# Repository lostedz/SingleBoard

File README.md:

# 68000 Verilog CPU

Target: **Xilinx Spartan-6 XC6SLX16 / FTG256 at 50 MHz** (speed grade -2
provisional). See `fpga/spartan6/README.md` for the ISE/XST
synthesis flow and board integration requirements.

An **MT48LC16M16A2-75 SDRAM controller** is included for the same 50 MHz clock.
See [SDRAM integration](docs/sdram.md) for its 32 MiB address mapping, CPU bus
connection, Spartan-6 clock forwarding, initialization and refresh behavior.
Run its standalone and CPU integration tests with `python scripts/test_sdram.py`.

A [memory-mapped UART](docs/uart.md) is available at **0xFF0000**, defaulting
to **115200 baud, 8N1** at 50 MHz. It includes TX/RX buffering, receive error
flags and optional interrupts. Run `python scripts/test_uart.py` for serial
and 68000 interrupt/echo tests.

A [schematic and board](hardware/README.md) for this target are in `hardware/`, as
a KiCad 10 project covering power, FPGA supply and configuration, the boot flash,
the SDRAM and the UART/clock/reset front panel. Both are generated:
`python scripts/gen_schematic.py` emits the drawing and the matching
`fpga/spartan6/singleboard.ucf` from one ball-assignment table, and
`python scripts/gen_pcb.py` builds the board from the schematic's own netlist —
a 120 × 90 mm four-layer placement whose floorplan follows which bank each
block's balls are in. The schematic passes ERC, the board passes DRC, and the
copper has been read back and compared to the assignment table. It is still a
concept: **the board has no tracks on it**, and there has been no ISE run and no
hardware validation.

`rtl/m68000.v` provides a synthesizable Verilog-2005 CPU for FPGA integration,
based on Frederic Requin's ISC-licensed [J68](https://github.com/fredrequin/j68_cpu).
The execution engine is vendored J68 RTL, not a newly written CPU. Local work
adds a 24-bit address interface, portable inferred memories, and executable
self-checking integration tests.

J68 implements the 68000 instruction set using a microcoded 16-bit datapath:
eight 32-bit data registers, eight address registers, separate user and
supervisor stacks, condition codes, effective-address decoding, multiply/divide,
traps, and autovectored interrupts. See `rtl/j68/PROVENANCE.md` for the pinned
revision and changes.

## Interface

All signals use one rising-edge clock. Inputs must be synchronous to `clk`.

| Signal | Meaning |
| --- | --- |
| `clk`, `reset` | Clock and active-high reset; hold reset for at least two clock edges and deassert synchronously |
| `clk_en` | CPU step enable; tie high for continuous execution |
| `ipl_n[2:0]` | Active-low encoded interrupt level; `111` is no interrupt, `101` is level 2 |
| `bus_valid` | Pending memory transaction |
| `bus_write` | 1 for write, 0 for read; meaningful while valid |
| `bus_addr[23:0]` | Byte address, including the low bit; high internal address bits are truncated to the 68000's 24-bit address space |
| `bus_be[1:0]` | Active-high byte lanes: bit 1 selects the even-address/high byte, bit 0 the odd-address/low byte |
| `bus_wdata[15:0]` | Write data already positioned in the selected lanes |
| `bus_rdata[15:0]` | Read data for the aligned word containing `bus_addr` |
| `bus_ready` | Memory acknowledgement; reads must have valid data on the completion edge |
| `bus_fc[2:0]` | J68 function-code output (user/supervisor, data/program/vector) |
| `debug_pc`, `debug_sr` | Internal 32-bit program counter and 16-bit status register |

A transfer completes on a rising edge when **`clk_en && bus_valid && bus_ready`**.
The memory slave must use that same condition for write side effects. Address,
direction, lanes, function code and write data remain stable during a pending
transaction, including CPU pauses. A slave may keep `bus_ready` high, or delay
it for any number of cycles. If the CPU is paused, retain read data/acknowledgement
until an enabled completion edge. Reset cancels a pending transaction.

Memory is big-endian. A longword uses two word transactions, high word first
for normal forward accesses. Fetch the initial SSP from addresses 0–3 and
initial PC from 4–7. Supply a valid reset-vector table and executable memory.
The testbench is a complete example memory slave.

## Build and test

Run from the project root so `$readmemb` can locate `rtl/j68/*.mem`. Include
every source in `rtl/files.f` and select `m68000` as the synthesis top. Memory
initialization must be supported by the target FPGA/toolchain; this is not
an ASIC ROM implementation. There are no vendor primitives or SystemVerilog
dependencies in the RTL.

With Python 3 and Icarus Verilog (`iverilog` and `vvp`) on PATH:

```sh
python scripts/test.py
python scripts/test.py --vcd
```

The runner also recognizes a local portable Windows installation in
`.tools/bin`. Test firmware is committed as `tests/smoke.hex`; an assembler
is not needed to run tests. To rebuild it with vasm:

```sh
vasmm68k -m68000 -Fbin -o build/smoke.bin tests/smoke.asm
python scripts/rom_to_hex.py
```

The self-checking program covers reset vectors, MOVE and MOVEQ, big-endian
byte/word/long transfers, postincrement/predecrement/indexed addressing,
arithmetic and overflow/carry/zero/negative flags, logic, shifts, bit operations,
DBRA, subroutine calls, signed/unsigned multiply/divide, MOVEM, TRAP/RTE,
STOP wakeup, and level-2 interrupts. It runs twice per simulation to check
reset recovery, with zero/one/seven wait cycles, periodic CPU pauses, and
deterministic irregular pauses with thirteen wait cycles. The bench also
checks request stability while stalled. Any failure or missing PASS fails
the Python runner, including with older VVP versions that return zero on `$fatal`.

## Compatibility limits

- This is not cycle-exact or a pin-compatible replacement for a physical MC68000.
  The interface is synchronous valid/ready, without AS/UDS/LDS, bus arbitration,
  a peripheral E clock, or a locked bus-cycle signal. External logic is needed
  for such system interfaces; multiprocessor atomic TAS is not provided.
- Bus-error exceptions and externally supplied interrupt vectors are not
  implemented. Interrupts use internal autovectors, without an external IACK cycle.
- J68's `RESET` opcode enters its CPU initialization routine; it does not emit
  the original processor's external peripheral-reset pulse.
- Address-error and other exception machinery comes from upstream. The included
  tests are smoke/integration coverage, not exhaustive instruction or exception
  conformance certification. No FPGA synthesis, timing closure, or hardware
  validation has been performed for this project.

Licensed under ISC; upstream attribution and licensing are retained.

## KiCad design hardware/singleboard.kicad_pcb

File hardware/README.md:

# SingleBoard 68K schematic and board

A KiCad schematic and board for the target the rest of this repository aims at: the
J68-derived 68000 soft CPU running inside an **XC6SLX16-FTG256** at 50 MHz, with the
**MT48LC16M16A2-75** SDRAM of [docs/sdram.md](../docs/sdram.md) and the 3.3 V
logic-level UART of [docs/uart.md](../docs/uart.md).

**This is a concept.** The schematic has not been simulated, fabricated or reviewed
by anyone, and the board is **placed but not routed** — it has no tracks on it at
all. Nothing here has been checked against silicon. Read
[Before you build one](#before-you-build-one) before spending money on it.

## Opening it

Open `singleboard.kicad_pro` in KiCad 10 (the files are written in KiCad 10's
formats: schematic `version 20260101`, board `version 20260206`).
`singleboard.pdf` is the drawing plotted out and `singleboard-pcb.pdf` is the
board's layer plot, if you only want to read them.

Project-specific symbols live in `symbols/singleboard.kicad_sym` and are found
through `sym-lib-table`. Everything else, footprints included, comes from KiCad's
stock libraries, so the board carries no local footprint library.

## Regenerating

Neither file is drawn by hand. The schematic comes first, and the board is
generated from the schematic's own netlist:

```sh
python scripts/gen_schematic.py
python scripts/gen_pcb.py
```

The first run writes the six sheets, the project symbol library, the project file
**and** `fpga/spartan6/singleboard.ucf`. The ball assignment exists once — the
SDRAM half is read from [sp6_SDRAM.ucf](../fpga/spartan6/sp6_SDRAM.ucf), the rest is
in the `BANK0_MAP` / `BANK2_MAP` tables at the top of the script — so the drawing and
the ISE constraints cannot drift apart. Edit the source, re-run; do not edit the
`.kicad_sch`, `.kicad_pcb`, `.kicad_pro` or `singleboard.ucf` by hand.

The second run exports the netlist from the schematic with `kicad-cli` and builds
the board from it, so footprints, references and nets cannot drift away from the
drawing either. It needs KiCad 10 installed and re-executes itself under KiCad's
bundled Python to get `pcbnew`; set `KICAD_HOME` if it is not in the usual place.

Before it draws anything the generator checks that every assigned ball exists on
the FTG256, is an I/O rather than a supply ball, and that the SDRAM sits wholly in
one bank. It fails loudly rather than emitting a wrong drawing.

The FPGA symbol itself is built from `sources/XC6SLX16-FTG256.lib`, so its 256
ball names and numbers are not retyped anywhere.

UUIDs are derived deterministically from sheet and reference names in both
generators, so regenerating an unchanged design produces byte-identical files.
`pcbnew` hands out random ones and sorts footprints by them, so the board
generator reseeds every item from its reference designator before saving.

## Sheets

| Page | Sheet | Contents |
| --- | --- | --- |
| 1 | `singleboard` | Overview and sheet index |
| 2 | `power` | 5 V input protection, 3.3 V and 1.2 V buck converters, test points |
| 3 | `fpga_core` | FPGA supply and ground balls, decoupling, configuration pins, boot flash, JTAG |
| 4 | `fpga_io` | The two I/O bank units, VCCO decoupling (A2 sheet) |
| 5 | `sdram` | MT48LC16M16A2P-75 and its decoupling |
| 6 | `io` | Oscillator, UART header, reset button, status LEDs |

Cross-sheet connectivity is by **global label**; the sheets carry no hierarchy
pins. Every device pin is drawn as a short stub terminated in a label or a power
port, which is the usual style for a part with this many pins and keeps the
generator honest.

## Power

Two rails from a 5 V barrel jack:

| Rail | Source | Feeds |
| --- | --- | --- |
| +3V3 | TPS562200 buck, 100k/30.1k feedback | VCCO banks 0–3, VCCAUX, SDRAM, boot flash, oscillator, LEDs |
| +1V2 | TPS562200 buck, 56.2k/100k feedback | VCCINT |

The input has a 1.1 A polyfuse, a series SS34 for reverse polarity (about 0.4 V
of drop; both bucks accept 4.5 V minimum) and an SMAJ5.0A clamp.

**VCCAUX is run at 3.3 V rather than 2.5 V**, which is what removes the third
rail. The bitstream has to agree, so the generated UCF carries
`CONFIG VCCAUX = 3.3;`.

R3/C3 hold the 3.3 V enable about 100 ms behind the 1.2 V enable, so VCCINT comes
up before VCCO and VCCAUX. This follows the recommended order; confirm against
DS162 whether your device actually requires a sequence.

Decoupling is one 100 nF per supply ball — 8 on VCCINT, 8 on VCCAUX, 20 across the
four VCCO banks, 7 on the SDRAM — plus bulk on each rail. They are only meaningful
if layout puts each one against its ball, which is what the board's
[bypass placement](#bypass-placement) is for.

## Pin assignment

**The SDRAM balls are not chosen here.** All 39 of them are read out of
[sp6_SDRAM.ucf](../fpga/spartan6/sp6_SDRAM.ucf), the constraints file for the
reference Spartan-6 SDRAM board, at generation time. Only the signal names are
translated (`Data[0]` → `SDRAM_DQ0`, `SDCS0` → `SDRAM_CS_N`, and so on); every
`LOC` is taken verbatim, so the schematic follows the physical board rather than
the other way round. Change that file and re-run the generator.

They all land in **bank 3**, and the generator refuses to run if they do not.
Note that the assignment does not line up with the hard memory controller's own
ball names — `SDRAM_DQ0` sits on `IO_L83N_VREF_3`, for instance. That is fine
here: the MCB is not instantiated, and the soft controller in
`rtl/sdram_mt48lc16m16a2.v` drives these as ordinary LVCMOS33 I/O.

Bank 0 carries the 50 MHz clock (on GCLK-capable ball E7), the UART, the reset
button, the four LEDs and the HSWAPEN strap. Bank 2 carries the master-SPI
configuration interface. **Bank 1 is entirely spare**, as is most of bank 0.

`sp6_SDRAM.ucf` also fixes four non-SDRAM pins for its own board — `CLK_50M_IN`
A10, `sys_rst_n` R7, `led_1` T9, `led_2` R9 — which this schematic does *not*
follow; its clock, reset and LEDs are on the bank-0 balls above. If the intent is
to match that board rather than to design a new one, those four should move too.

Unused bank pins carry a no-connect flag. To bring one out later, delete its flag
on the `fpga_io` sheet and add a `LOC` to the UCF.

`R30` (22 Ω) damps the forwarded SDRAM clock. The FPGA-side net is
`SDRAM_CLK_FPGA` and the device-side net is `SDRAM_CLK`;
`rtl/sdram_spartan6_clock.v` drives the FPGA side from an ODDR2 with the clock
inverted so the device samples mid-cycle.

## Configuration

Master SPI from a W25Q32JVSS (32 Mbit; an XC6SLX16 bitstream is about 3.73 Mbit),
with JTAG on a 6-pin 0.1" header in the Digilent order (1 TMS, 2 TDI, 3 TDO,
4 TCK, 5 GND, 6 VREF).

The mode pins are strapped **M[1:0] = 01**. Each strap has a fitted resistor and a
DNP alternate (R16 and R17) so the mode can be changed by rework.
DONE gets the 330 Ω pull-up UG380 asks for; D4 lights while the device is
*un*configured.

## Board

`singleboard.kicad_pcb` is **120 × 90 mm, four layers, placed and planed but with
no tracks on it**. All 129 footprints are down, every pad carries the net the
schematic gives it (bar the barrel jack's unused switched contact), the
planes are poured, and all 220 nets are still ratsnest lines. Routing it is the
next piece of work, not something this file has had.

| Layer | Use |
| --- | --- |
| F.Cu | Components and signal routing |
| In1.Cu (`GND`) | Solid ground plane, 10466 mm² poured |
| In2.Cu (`PWR`) | +3V3 plane with a 1180 mm² +1V2 island cut into it |
| B.Cu | Bypass capacitors, ground pour, signal routing |

Design rules live in `singleboard.kicad_pro` and are sized for an escape out of a
1.0 mm pitch BGA: 0.15 mm track on 0.13 mm clearance with 0.45/0.25 mm vias by
default, and a `Power` class at 0.6 mm track and 0.8/0.4 mm vias for GND, +5V,
+3V3, +1V2 and the two buck switch nodes.

### Floorplan

Nothing about the arrangement is arbitrary — each block sits on the side of the
package its balls are on, which the generator reads out of the same ball map the
schematic uses:

| Block | Where | Why |
| --- | --- | --- |
| SDRAM, `R30` | Left of the FPGA | All 39 SDRAM balls are in bank 3, the −X side |
| Oscillator, reset, LEDs, UART header | Above it | Bank 0 is the −Y side |
| Boot flash, mode straps, JTAG header, PROG | Below it | Bank 2 is the +Y side |
| Both bucks, barrel jack, fuse, TVS, test points | Right-hand column | Bank 1 is entirely spare, so nothing competes for it |

The 1.2 V island on In2.Cu is one connected region spanning the FPGA core, the
1.2 V buck and a neck between them; +3V3 fills the rest of that layer, and the
two are resolved by zone priority rather than by a hand-drawn split.

### Bypass placement

The 36 FPGA bypass capacitors are on the **back**, in the ball shadow. Each one is
assigned to a specific supply ball — `C100`–`C107` to the eight VCCINT balls,
`C120`–`C127` to the eight VCCAUX balls, `C200`–`C219` to the twenty VCCO balls,
in ball order — and then placed on the free slot nearest that ball, closest pair
first. The middle of the package is where the VCCINT cluster is, so it gets the
middle slots.

A 0402 is 1.91 × 1.01 mm and the FTG256 balls are on a 1.0 mm pitch, so one cap
cannot sit centred on every ball; the slot grid is 2.2 × 1.8 mm, which clears the
courtyards both ways. Their reference designators are on the fab layer only —
there is no room to letter them on silkscreen at that pitch. The seven SDRAM caps
are likewise on the back, in a column under the body.

## What has been checked

Run against the generated files with KiCad 10.0.6:

- **ERC: 0 violations** (`kicad-cli sch erc`), errors and warnings.
- **Netlist**: 220 nets. Every net in the assignment tables was confirmed to reach
  the intended FPGA ball, every SDRAM signal was confirmed to reach the intended
  TSOP pin, and every `LOC` in the generated UCF was confirmed against the
  exported netlist. No net has fewer than two nodes apart from the deliberate
  no-connects.
- **SDRAM balls**: all 39 `LOC` values in the generated UCF compared equal to
  `sp6_SDRAM.ucf`, and all 39 are bank-3 I/O balls on the FTG256.
- **Plot**: no content falls outside any sheet frame and no two text strings
  overlap on any sheet.
- **DRC: 0 errors, 1 warning** (`kicad-cli pcb drc`), run by `gen_pcb.py` itself
  on every generation; it exits non-zero if an error appears. The warning is an
  isolated copper fill on the +1V2 island, which is inherent to an unrouted
  board: nothing on an outer layer reaches In2.Cu until there are vias. The 252
  unconnected items are the unrouted nets.
- **Copper against the assignment**: all 55 assigned balls were read back off the
  board and compared to the generator's tables; every one carries the intended
  net. All 39 SDRAM signals land on the intended FTG256 ball, all 38 device-side
  ones reach the intended TSOP pin, and the clock reaches pin 38 through `R30`.
  Every VCCINT, VCCAUX, VCCO and GND ball is on the rail it should be.
- **Placement**: every footprint except `J1` is wholly inside the outline, which
  the generator checks and refuses to write a board otherwise; `J1`'s barrel is
  meant to reach the edge. No courtyards overlap and no silkscreen collides,
  which is what the clean DRC above covers.
- **Reproducibility**: both generators were run twice from scratch and produced
  byte-identical `.kicad_sch`, `.kicad_pcb` and `.kicad_pro`.

## Before you build one

None of the following has been done, and each could change the design:

- **No routing.** The board is placed and poured, and that is all. Every net is
  still a ratsnest line. The FTG256 escape has not been attempted, so whether 220
  nets actually get out of that package on four layers — and whether four layers
  are enough — is an open question; a real escape usually wants via-in-pad or
  more layers, and finding out could push the bypass caps somewhere else.
- **No signal or power integrity work.** No stackup or impedance target, no
  length or skew matching on the SDRAM bus at 50 MHz, no return-path analysis
  across the In2.Cu plane split, no thermal work on the two bucks.
- **No fabrication outputs.** No gerbers, no drill file, no pick-and-place, no
  BOM. The design rules in the project file are a plausible four-layer
  capability, not a quote from a fab.
- **No ISE run.** The UCF has never been through MAP, PAR or static timing. Bank
  and clock-region legality of the assignment is unverified, as is whether the
  design fits and closes timing.
- **No supply validation.** Rail currents are estimates (VCCINT ~0.3 A,
  VCCAUX+VCCO ~0.4 A, SDRAM ~0.15 A). Inductor and capacitor values were chosen by
  convention, not calculated against a load profile or checked for loop stability.
- **Datasheet cross-checks still owed.** In particular: the SDRAM pin numbers
  (drawn to the JEDEC 54-pin TSOP-II arrangement), the Spartan-6 configuration
  mode encoding against UG380 Table 2-3, and the VCCAUX = 3.3 V choice against
  DS162 for the speed grade you buy.
- **The speed grade is still provisional** (-2), as noted in
  [fpga/spartan6/README.md](../fpga/spartan6/README.md).
- **There is no board-level top module yet.** The UCF names ports after
  `rtl/sdram_mt48lc16m16a2.v`, `rtl/uart_mmio.v` and `rtl/sdram_spartan6_clock.v`;
  something still has to instantiate the CPU, the memory arbiter, the boot ROM and
  the UART together and bring those ports out.

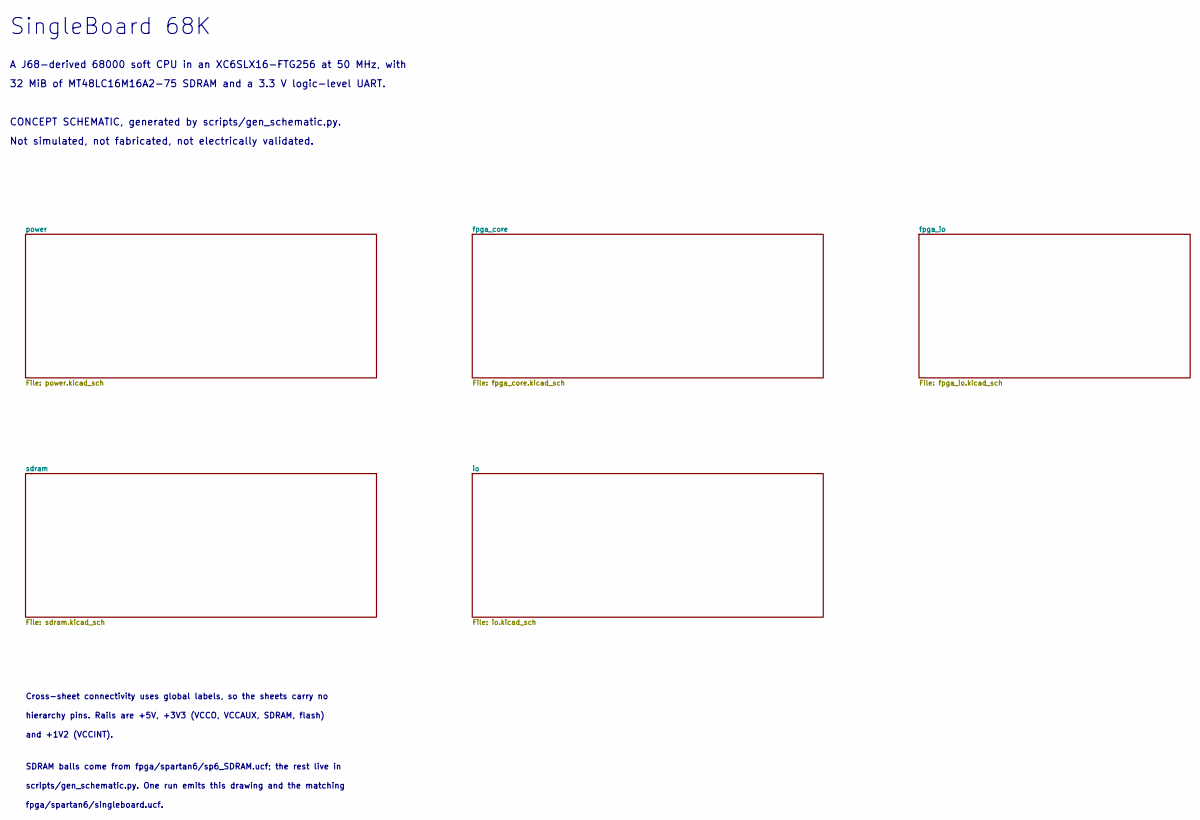
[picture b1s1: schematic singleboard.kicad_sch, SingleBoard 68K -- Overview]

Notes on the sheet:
SingleBoard 68K
A J68-derived 68000 soft CPU in an XC6SLX16-FTG256 at 50 MHz, with
32 MiB of MT48LC16M16A2-75 SDRAM and a 3.3 V logic-level UART.
CONCEPT SCHEMATIC, generated by scripts/gen_schematic.py.
Not simulated, not fabricated, not electrically validated.
Cross-sheet connectivity uses global labels, so the sheets carry no
hierarchy pins. Rails are +5V, +3V3 (VCCO, VCCAUX, SDRAM, flash)
and +1V2 (VCCINT).
SDRAM balls come from fpga/spartan6/sp6_SDRAM.ucf; the rest live in
scripts/gen_schematic.py. One run emits this drawing and the matching
fpga/spartan6/singleboard.ucf.

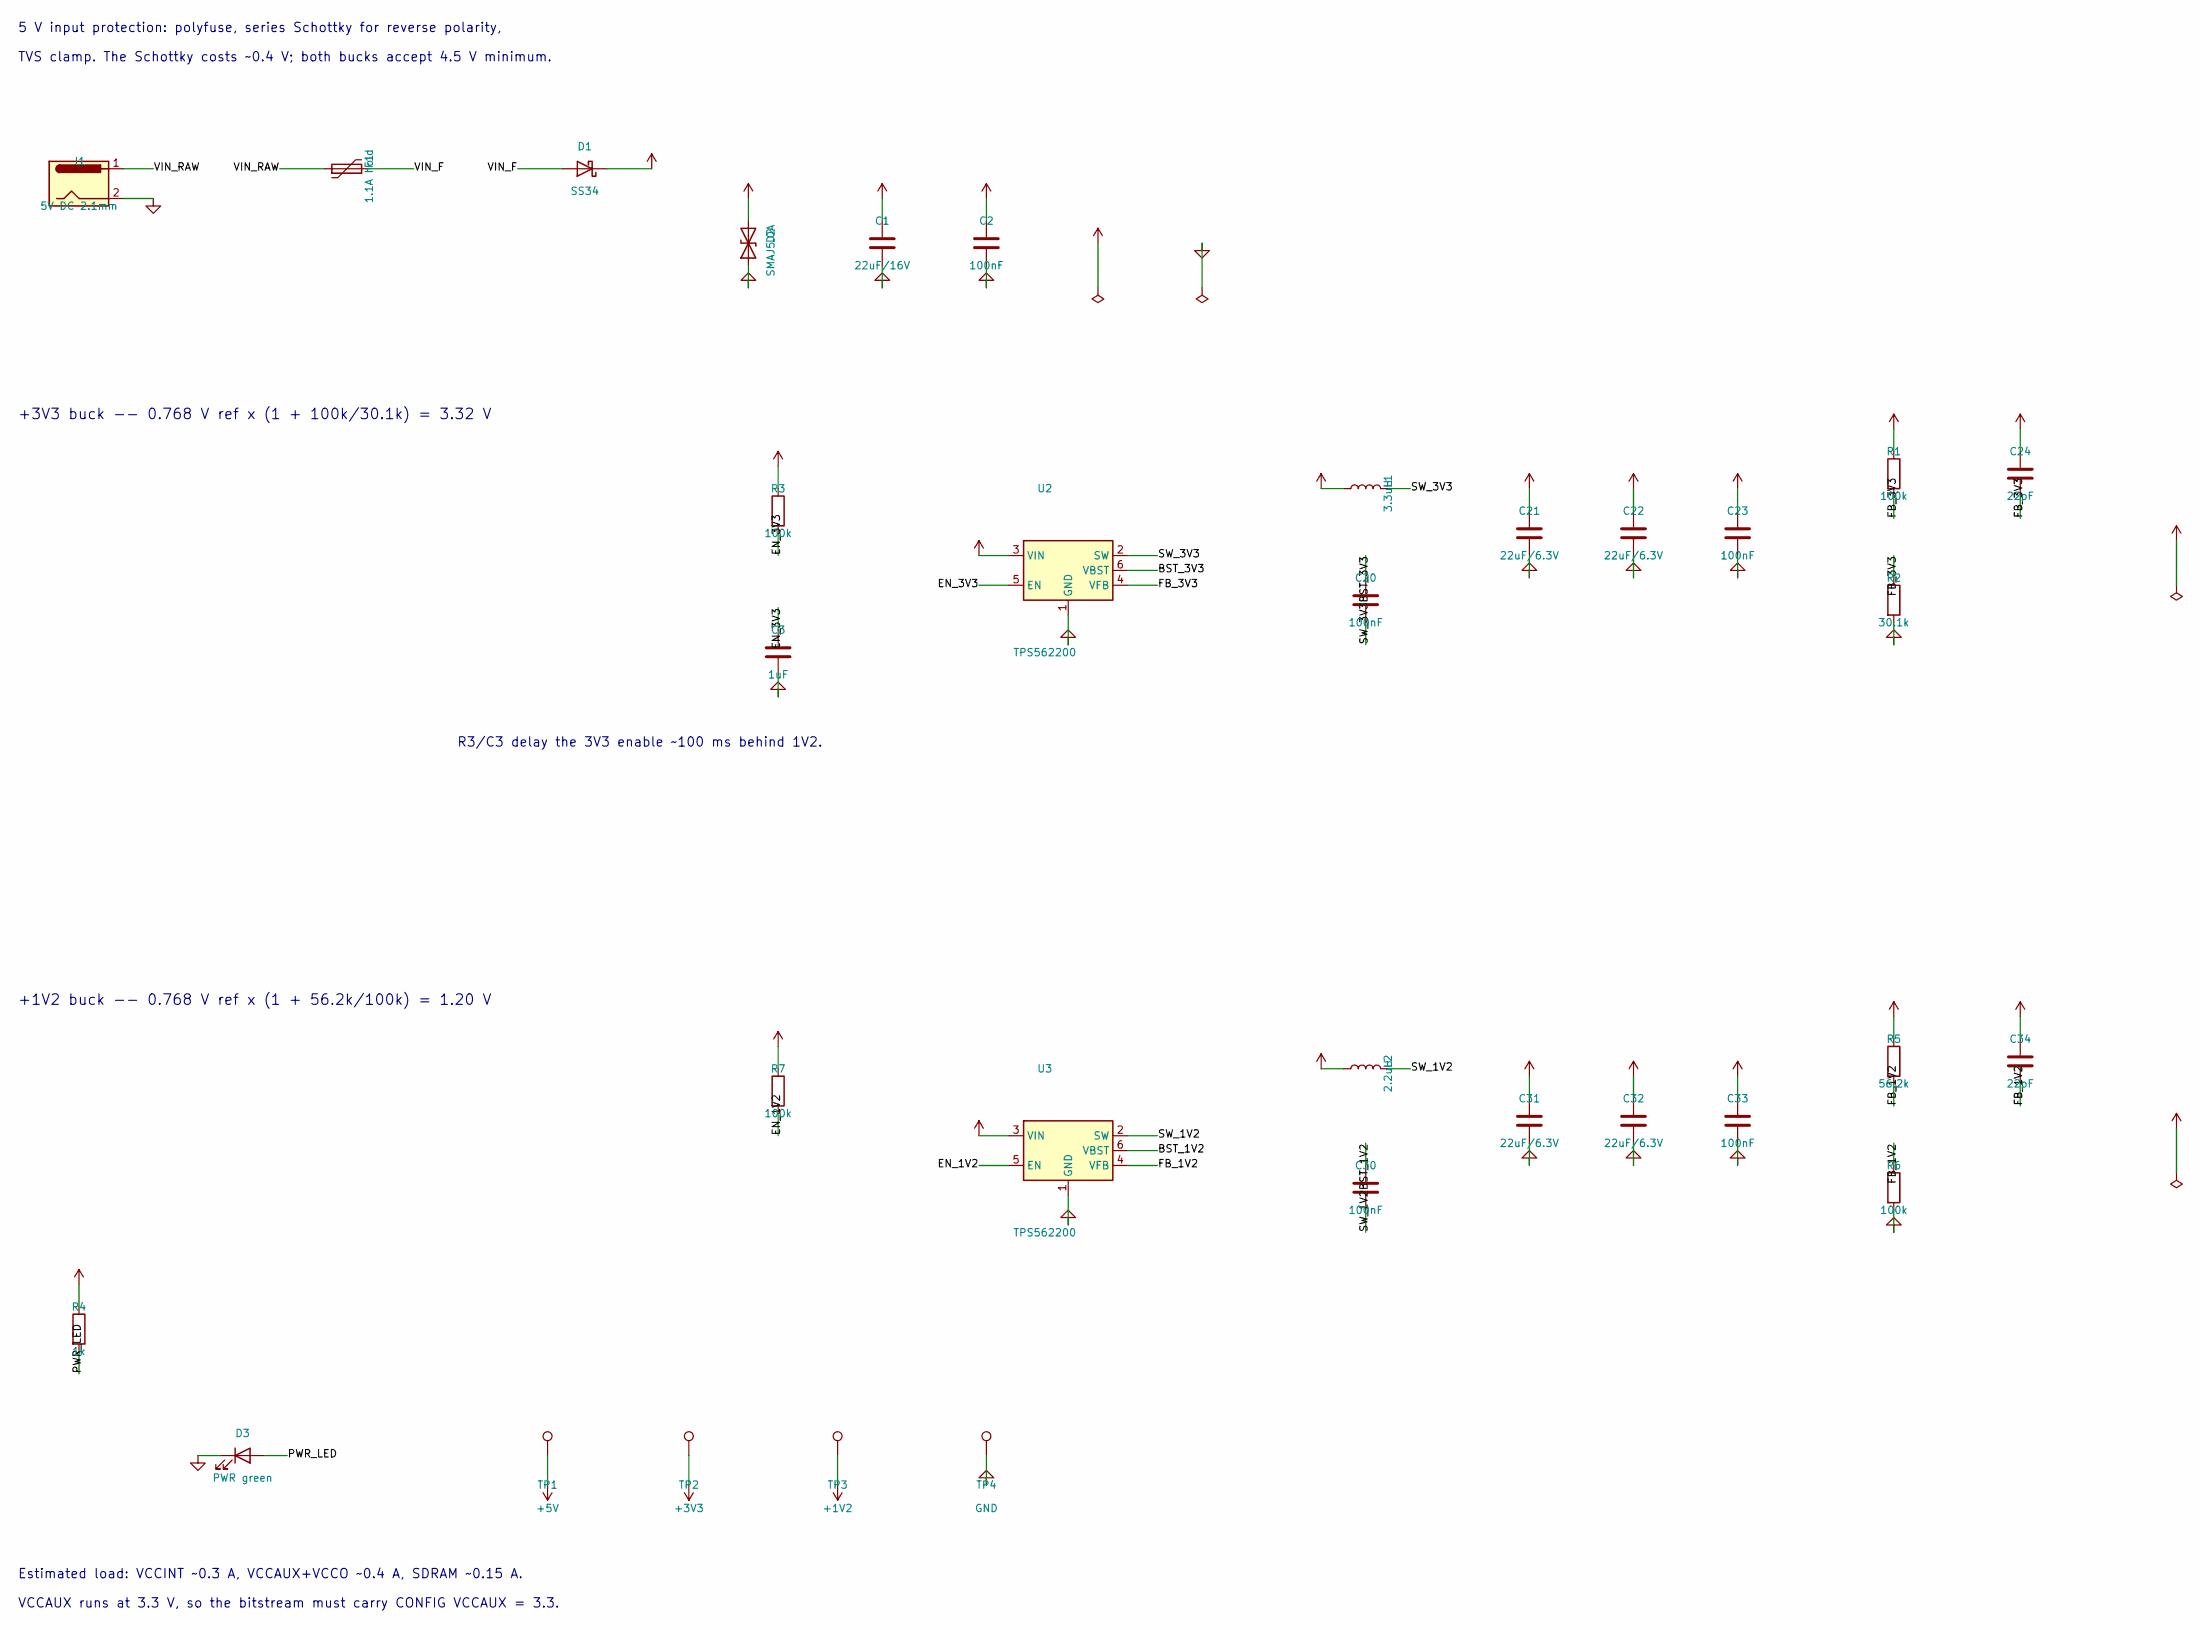
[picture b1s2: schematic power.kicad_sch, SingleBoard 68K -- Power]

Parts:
C1: 22uF/16V; C_1206_3216Metric
C2, C20, C23, C30, C33: 100nF; C_0402_1005Metric
C3: 1uF; C_0402_1005Metric
C21, C22, C31, C32: 22uF/6.3V; C_0805_2012Metric
C24, C34: 22pF; C_0402_1005Metric
D1: SS34; D_SMA
D2: SMAJ5.0A; D_SMA
D3: PWR green; LED_0603_1608Metric
F1: 1.1A hold; Fuse_1812_4532Metric
J1: 5V DC 2.1mm; BarrelJack_Horizontal
L1: 3.3uH; L_Bourns-SRN4018
L2: 2.2uH; L_Bourns-SRN4018
R1, R3, R6, R7: 100k; R_0402_1005Metric
R2: 30.1k; R_0402_1005Metric
R4: 1k; R_0402_1005Metric
R5: 56.2k; R_0402_1005Metric
TP1: +5V; TestPoint_Pad_D1.5mm
TP2: +3V3; TestPoint_Pad_D1.5mm
TP3: +1V2; TestPoint_Pad_D1.5mm
TP4: GND; TestPoint_Pad_D1.5mm
U2, U3: TPS562200; SOT-23-6

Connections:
+1V2: C31.1, C32.1, C33.1, C34.1, L2.1, R5.1, TP3.1; also elsewhere on the board
+3V3: C21.1, C22.1, C23.1, C24.1, L1.1, R1.1, R4.1, TP2.1; also elsewhere on the board
+5V: C1.1, C2.1, D1.1 (K), D2.2 (A2), R3.1, R7.1, TP1.1, U2.3 (VIN), U3.3 (VIN)
/power/BST_1V2: C30.1, U3.6 (VBST)
/power/BST_3V3: C20.1, U2.6 (VBST)
/power/EN_1V2: R7.2, U3.5 (EN)
/power/EN_3V3: C3.1, R3.2, U2.5 (EN)
/power/FB_1V2: C34.2, R5.2, R6.1, U3.4 (VFB)
/power/FB_3V3: C24.2, R1.2, R2.1, U2.4 (VFB)
/power/PWR_LED: D3.2 (A), R4.2
/power/SW_1V2: C30.2, L2.2, U3.2 (SW)
/power/SW_3V3: C20.2, L1.2, U2.2 (SW)
/power/VIN_F: D1.2 (A), F1.2
/power/VIN_RAW: F1.1, J1.1
GND: C1.2, C2.2, C3.2, C21.2, C22.2, C23.2, C31.2, C32.2, C33.2, D2.1 (A1), D3.1 (K), J1.2, R2.2, R6.2, TP4.1, U2.1 (GND), U3.1 (GND); also elsewhere on the board

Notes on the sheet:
5 V input protection: polyfuse, series Schottky for reverse polarity,
TVS clamp. The Schottky costs ~0.4 V; both bucks accept 4.5 V minimum.
+3V3 buck -- 0.768 V ref x (1 + 100k/30.1k) = 3.32 V
+1V2 buck -- 0.768 V ref x (1 + 56.2k/100k) = 1.20 V
R3/C3 delay the 3V3 enable ~100 ms behind 1V2.
Estimated load: VCCINT ~0.3 A, VCCAUX+VCCO ~0.4 A, SDRAM ~0.15 A.
VCCAUX runs at 3.3 V, so the bitstream must carry CONFIG VCCAUX = 3.3.

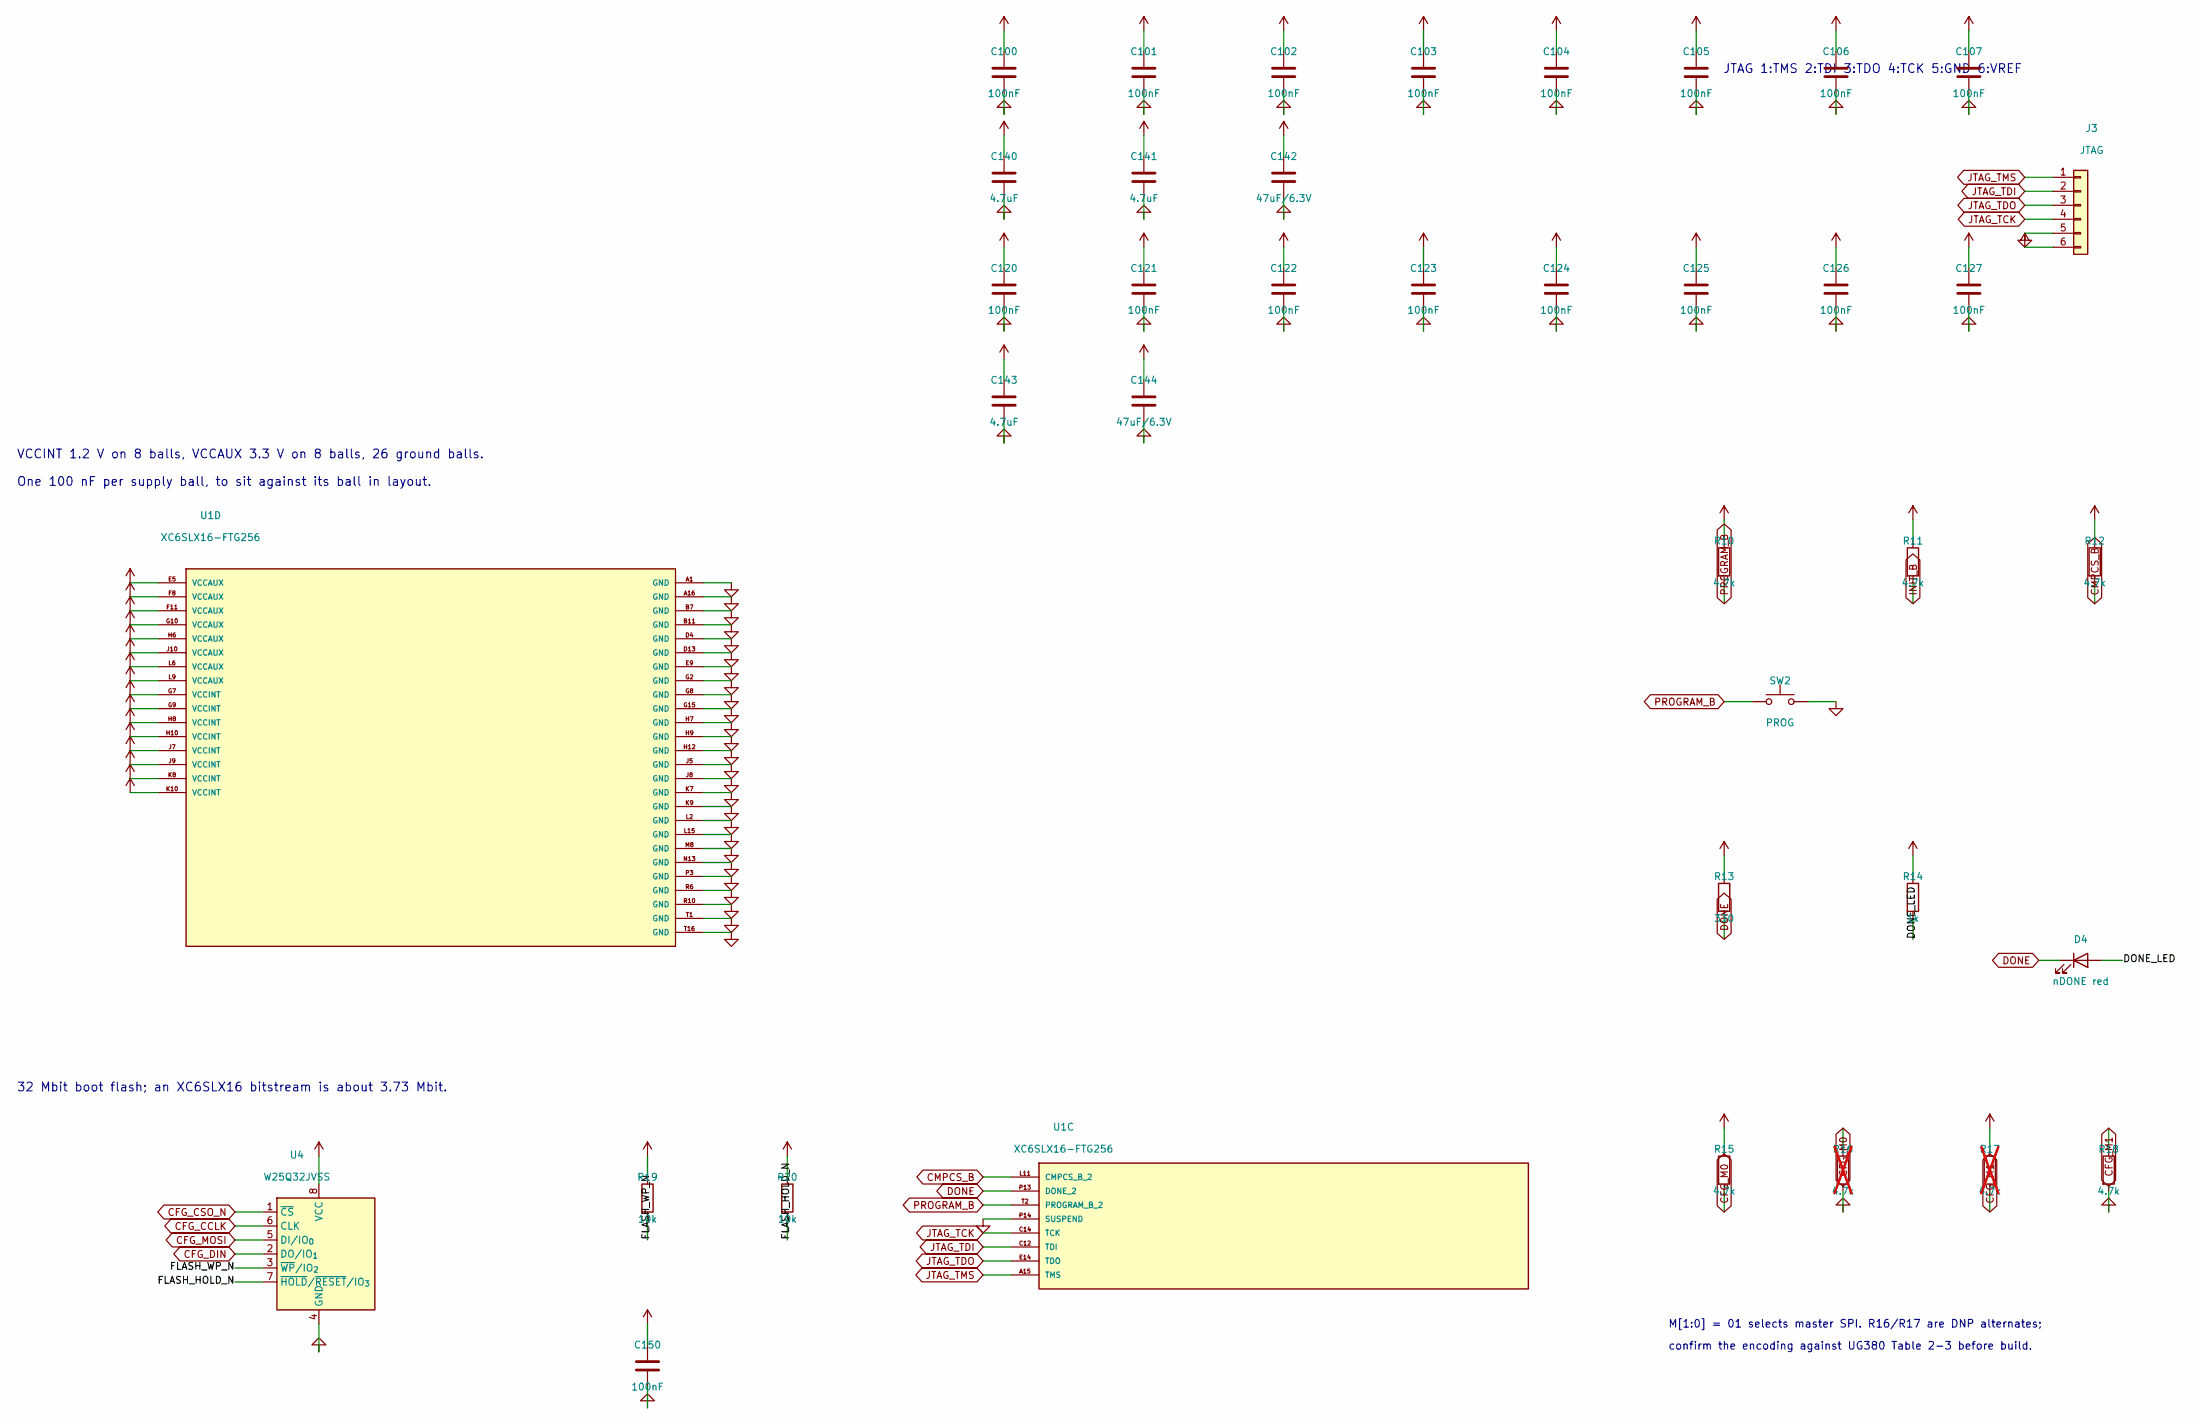
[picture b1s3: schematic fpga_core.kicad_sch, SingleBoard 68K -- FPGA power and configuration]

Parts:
C100, C101, C102, C103, C104, C105, C106, C107, C120, C121, C122, C123, C124, C125, C126, C127, C150: 100nF; C_0402_1005Metric
C140, C141, C143: 4.7uF; C_0805_2012Metric
C142, C144: 47uF/6.3V; C_1206_3216Metric
D4: nDONE red; LED_0603_1608Metric
J3: JTAG; PinHeader_1x06_P2.54mm_Vertical
R10, R11, R12, R15, R18: 4.7k; R_0402_1005Metric
R13: 330; R_0402_1005Metric
R14: 1k; R_0402_1005Metric
R16, R17: 4.7k; R_0402_1005Metric; not fitted
R19, R20: 10k; R_0402_1005Metric
SW2: PROG; SW_SPST_SKQG_WithStem
U1: XC6SLX16-FTG256; Xilinx_FTG256
U4: W25Q32JVSS; SOIC-8_5.3x5.3mm_P1.27mm

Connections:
+1V2: C100.1, C101.1, C102.1, C103.1, C104.1, C105.1, C106.1, C107.1, C140.1, C141.1, C142.1, U1.G7 (VCCINT), U1.G9 (VCCINT), U1.H8 (VCCINT), U1.H10 (VCCINT), U1.J7 (VCCINT), U1.J9 (VCCINT), U1.K8 (VCCINT), U1.K10 (VCCINT); also elsewhere on the board
+3V3: C120.1, C121.1, C122.1, C123.1, C124.1, C125.1, C126.1, C127.1, C143.1, C144.1, C150.1, J3.6, R10.1, R11.1, R12.1, R13.1, R14.1, R15.1, R17.1, R19.1, R20.1, U1.E5 (VCCAUX), U1.F8 (VCCAUX), U1.F11 (VCCAUX), U1.G10 (VCCAUX), U1.H6 (VCCAUX), U1.J10 (VCCAUX), U1.L6 (VCCAUX), U1.L9 (VCCAUX), U4.8 (VCC); also elsewhere on the board
/fpga_core/DONE_LED: D4.2 (A), R14.2
/fpga_core/FLASH_HOLD_N: R20.2, U4.7 (~HOLD/~RESET/IO_{3})
/fpga_core/FLASH_WP_N: R19.2, U4.3 (~WP/IO_{2})
CFG_CCLK: U4.6 (CLK); also elsewhere on the board
CFG_CSO_N: U4.1 (~CS); also elsewhere on the board
CFG_DIN: U4.2 (DO/IO_{1}); also elsewhere on the board
CFG_M0: R15.2, R16.1; also elsewhere on the board
CFG_M1: R17.2, R18.1; also elsewhere on the board
CFG_MOSI: U4.5 (DI/IO_{0}); also elsewhere on the board
CMPCS_B: R12.2, U1.L11 (CMPCS_B_2)
DONE: D4.1 (K), R13.2, U1.P13 (DONE_2)
GND: C100.2, C101.2, C102.2, C103.2, C104.2, C105.2, C106.2, C107.2, C120.2, C121.2, C122.2, C123.2, C124.2, C125.2, C126.2, C127.2, C140.2, C141.2, C142.2, C143.2, C144.2, C150.2, J3.5, R16.2, R18.2, SW2.2, U1.A1 (GND), U1.A16 (GND), U1.B7 (GND), U1.B11 (GND), U1.D4 (GND), U1.D13 (GND), U1.E9 (GND), U1.G2 (GND), U1.G8 (GND), U1.G15 (GND), U1.H7 (GND), U1.H9 (GND), U1.H12 (GND), U1.J5 (GND), U1.J8 (GND), U1.K7 (GND), U1.K9 (GND), U1.L2 (GND), U1.L15 (GND), U1.M8 (GND), U1.N13 (GND), U1.P3 (GND), U1.P14 (SUSPEND), U1.R6 (GND), U1.R10 (GND), U1.T1 (GND), U1.T16 (GND), U4.4 (GND); also elsewhere on the board
INIT_B: R11.2; also elsewhere on the board
JTAG_TCK: J3.4, U1.C14 (TCK)
JTAG_TDI: J3.2, U1.C12 (TDI)
JTAG_TDO: J3.3, U1.E14 (TDO)
JTAG_TMS: J3.1, U1.A15 (TMS)
PROGRAM_B: R10.2, SW2.1, U1.T2 (PROGRAM_B_2)

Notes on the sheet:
VCCINT 1.2 V on 8 balls, VCCAUX 3.3 V on 8 balls, 26 ground balls.
One 100 nF per supply ball, to sit against its ball in layout.
M[1:0] = 01 selects master SPI. R16/R17 are DNP alternates;
confirm the encoding against UG380 Table 2-3 before build.
32 Mbit boot flash; an XC6SLX16 bitstream is about 3.73 Mbit.
JTAG 1:TMS 2:TDI 3:TDO 4:TCK 5:GND 6:VREF
